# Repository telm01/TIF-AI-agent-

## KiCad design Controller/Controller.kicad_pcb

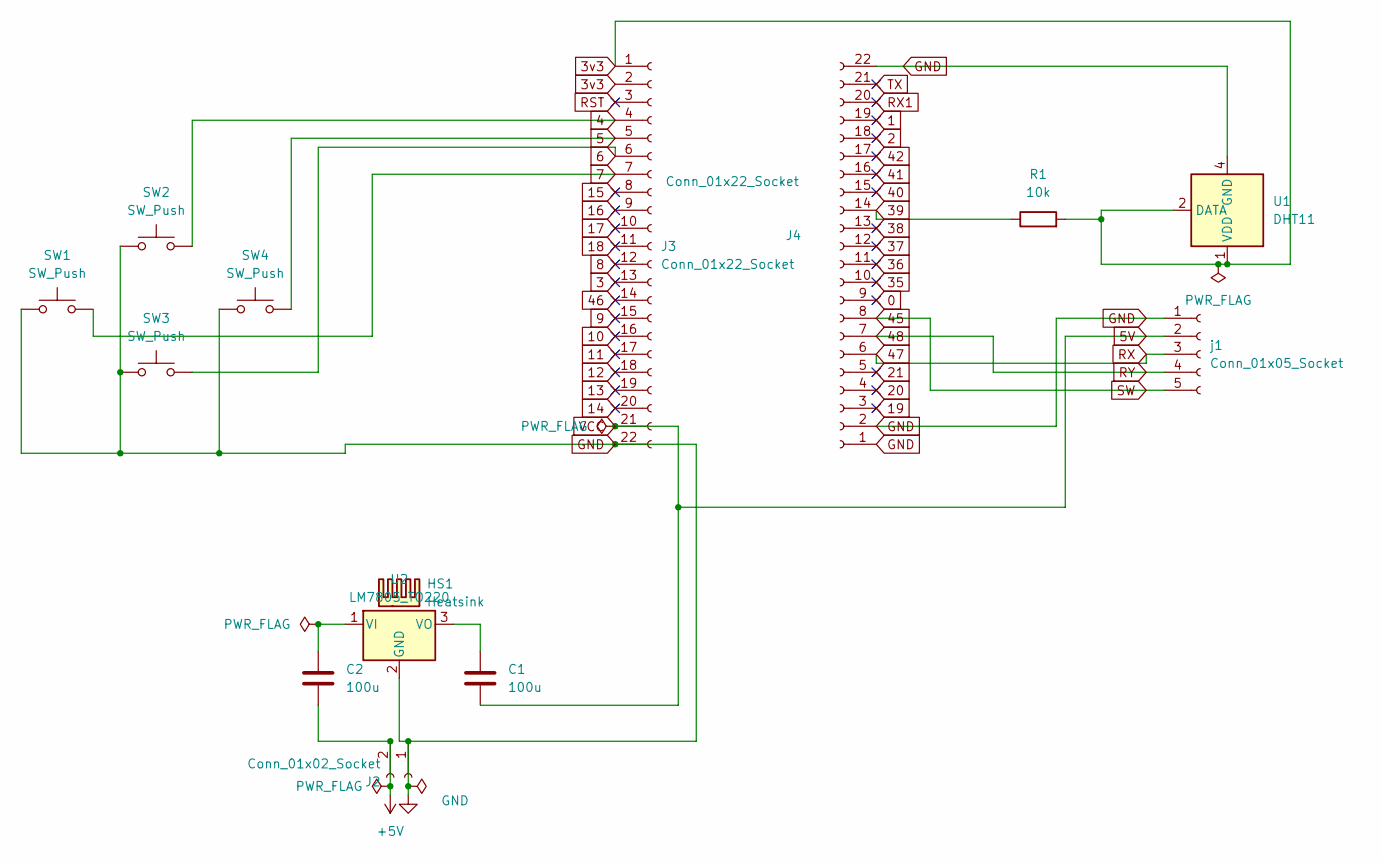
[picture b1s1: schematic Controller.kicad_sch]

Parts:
C1, C2: 100u; C_Radial_D5.0mm_H11.0mm_P2.00mm
HS1: Heatsink; Heatsink_Stonecold_HS-S01_13.21x6.35mm
J2: Conn_01x02_Socket; PinHeader_1x02_P2.54mm_Vertical
J3, J4: Conn_01x22_Socket; PinSocket_1x22_P2.00mm_Vertical
R1: 10k; R_Axial_DIN0204_L3.6mm_D1.6mm_P7.62mm_Horizontal
SW1, SW2, SW3, SW4: SW_Push; SW_Push_1P1T_NO_CK_PTS125Sx43PSMTR
U1: DHT11; Aosong_DHT11_5.5x12.0_P2.54mm
U2: LM7805_TO220; TO-220-3_Vertical
j1: Conn_01x05_Socket; PinSocket_1x05_P2.00mm_Horizontal

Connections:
0: J4.9
1: J4.19
2: J4.18
3: J3.13
3v3: J3.1, J3.2, R1.2, U1.1 (VDD), U1.2 (DATA)
4: J3.4, SW2.2
5: J3.5, SW4.2
5V: C1.2, J3.21, j1.2
6: J3.6, SW3.2
7: J3.7, SW1.2
8: J3.12
9: J3.15
10: J3.16
11: J3.17
12: J3.18
13: J3.19
14: J3.20
15: J3.8
16: J3.9
17: J3.10
18: J3.11
19: J4.3
20: J4.4
21: J4.5
35: J4.10
36: J4.11
37: J4.12
38: J4.13
39: J4.14, R1.1
40: J4.15
41: J4.16
42: J4.17
46: J3.14
48: J4.7, j1.4
+5V: C2.2, J2.2
GND: J2.1, J3.22, J4.1, J4.2, J4.22, SW1.1, SW2.1, SW3.1, SW4.1, U1.4 (GND), U2.2 (GND), j1.1
unnamed: C2.1, U2.1 (VI)
unnamed: C1.1, U2.3 (VO)
RST: J3.3
TX: J4.21

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
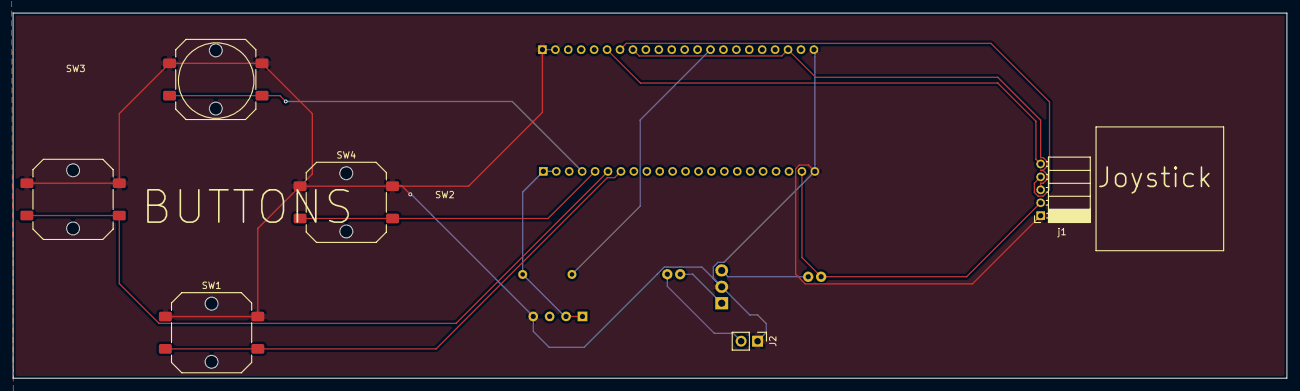
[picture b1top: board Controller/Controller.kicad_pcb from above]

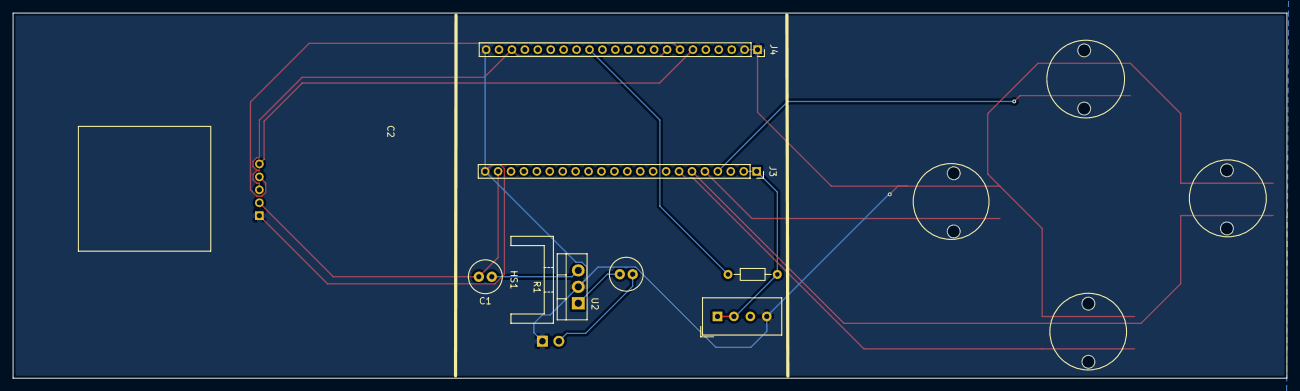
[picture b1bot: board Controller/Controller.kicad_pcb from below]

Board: 2 copper layers, 197.1 x 56.5 mm, 14 parts (8 on the bottom side), 14 nets.

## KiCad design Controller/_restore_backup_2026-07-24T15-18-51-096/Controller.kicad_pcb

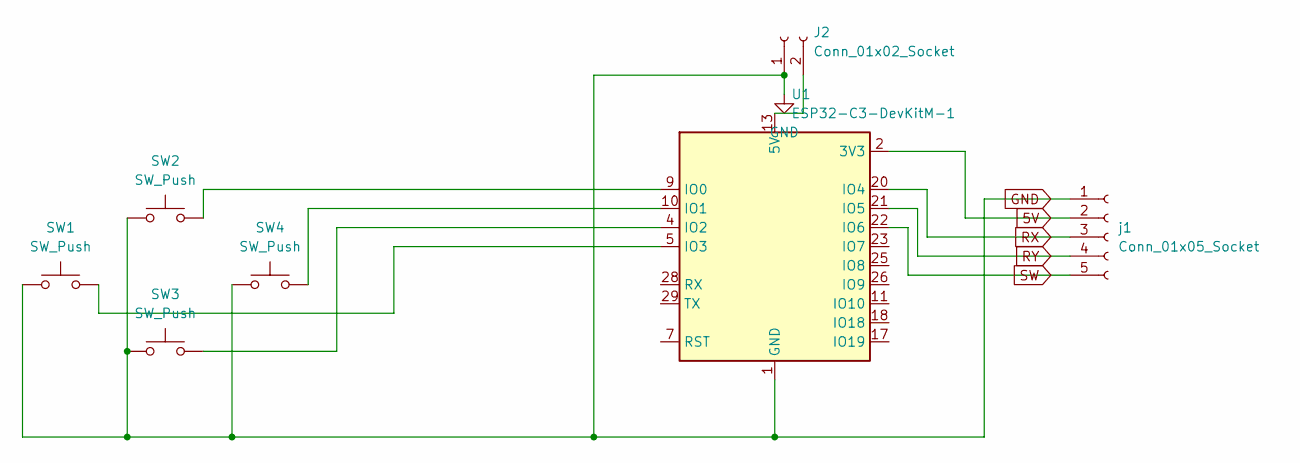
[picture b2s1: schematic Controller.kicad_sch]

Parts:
J2: Conn_01x02_Socket; PinHeader_1x02_P2.54mm_Vertical
SW1, SW2, SW3, SW4: SW_Push; SW_Push_1P1T_NO_CK_PTS125Sx43PSMTR
U1: ESP32-C3-DevKitM-1
j1: Conn_01x05_Socket; PinHeader_1x05_P2.54mm_Vertical

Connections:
5V: U1.2 (3V3), U1.3 (3V3), j1.2
GND: J2.1, SW1.1, SW2.1, SW3.1, SW4.1, U1.1 (GND), U1.6 (GND), U1.8 (GND), U1.12 (GND), U1.15 (GND), U1.16 (GND), U1.19 (GND), U1.24 (GND), U1.27 (GND), U1.30 (GND), j1.1
unnamed: J2.2, U1.13 (5V), U1.14 (5V)
unnamed: SW2.2, U1.9 (IO0)
unnamed: SW4.2, U1.10 (IO1)
unnamed: SW3.2, U1.4 (IO2)
unnamed: SW1.2, U1.5 (IO3)
RX: U1.20 (IO4), j1.3
RY: U1.21 (IO5), j1.4
SW: U1.22 (IO6), j1.5

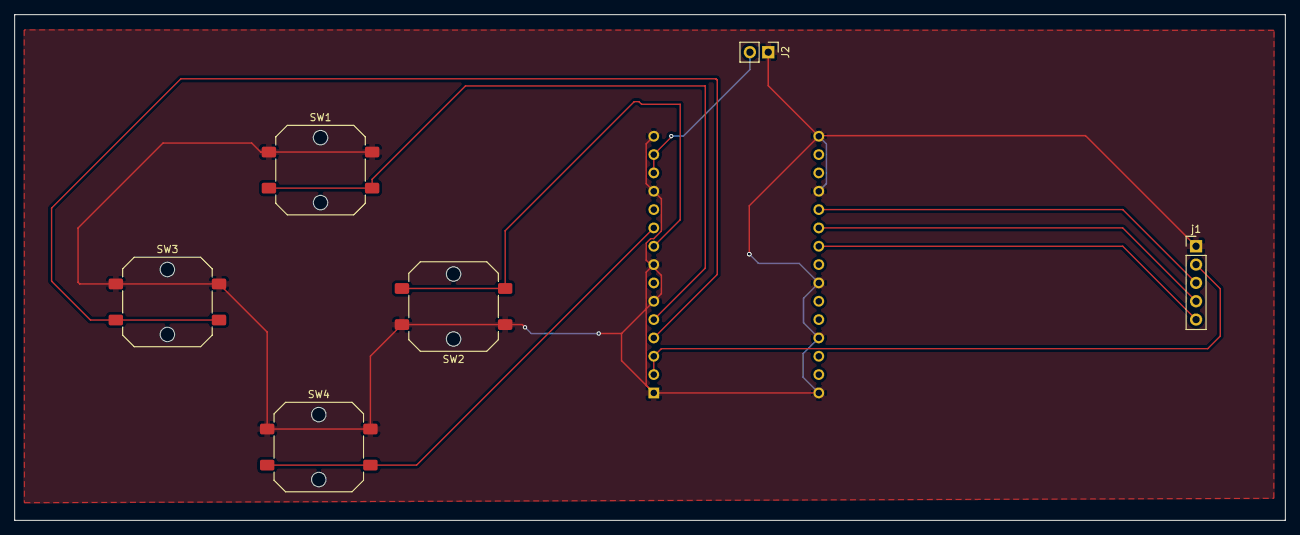
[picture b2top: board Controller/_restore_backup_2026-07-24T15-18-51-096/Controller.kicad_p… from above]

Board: 2 copper layers, 176.0 x 70.1 mm, 7 parts (1 on the bottom side), 10 nets.

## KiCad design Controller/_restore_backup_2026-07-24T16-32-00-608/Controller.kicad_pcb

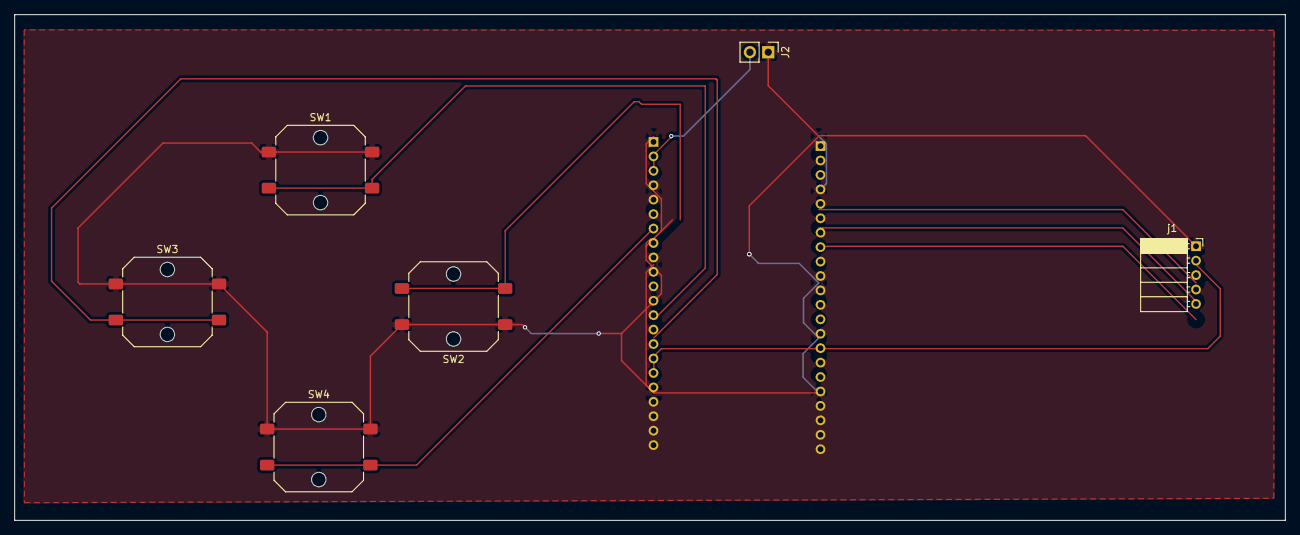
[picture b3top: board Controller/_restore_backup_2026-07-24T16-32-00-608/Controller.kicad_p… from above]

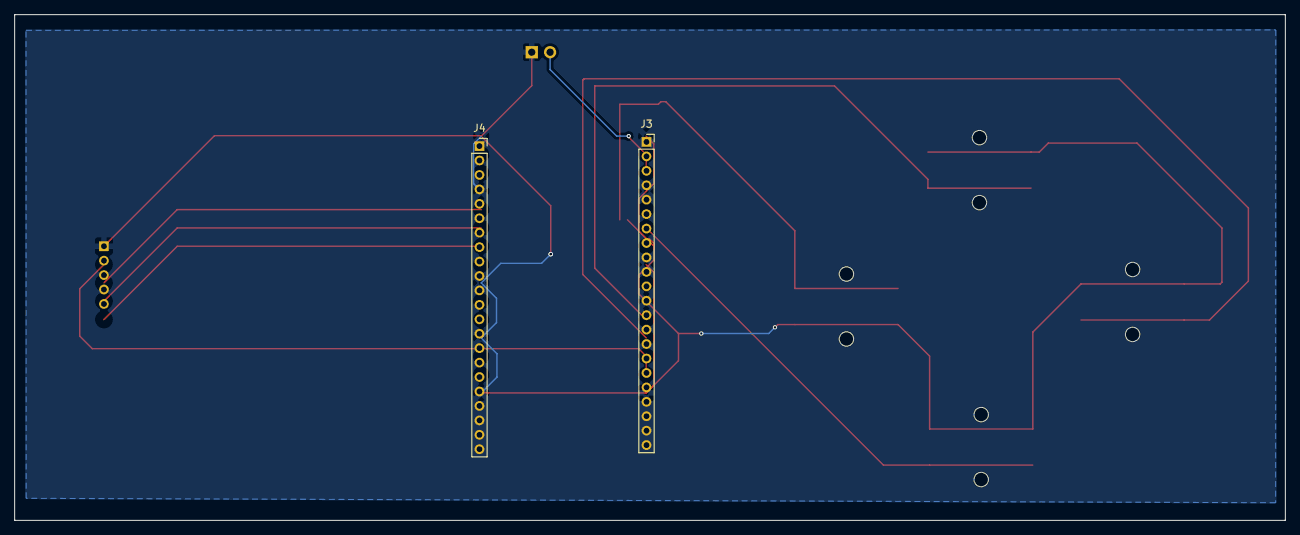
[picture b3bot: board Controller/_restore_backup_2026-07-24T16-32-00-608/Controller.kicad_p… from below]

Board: 2 copper layers, 176.0 x 70.1 mm, 8 parts (2 on the bottom side), 3 nets.

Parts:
J2: Conn_01x02_Socket; PinHeader_1x02_P2.54mm_Vertical
J3, J4: Conn_01x22_Socket; PinSocket_1x22_P2.00mm_Vertical
SW1, SW2, SW3, SW4: SW_Push; SW_Push_1P1T_NO_CK_PTS125Sx43PSMTR
j1: Conn_01x05_Socket; PinSocket_1x05_P2.00mm_Horizontal

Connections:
GND: J2.1, j1.1
unnamed: SW1.1 (1_1), SW2.1 (1_1), SW3.1 (1_1), SW4.1 (1_1)
RX: j1.3, j1.4, j1.5
